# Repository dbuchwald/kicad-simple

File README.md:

# kicad-simple
Simple designs in KiCAD that do not require separate projects

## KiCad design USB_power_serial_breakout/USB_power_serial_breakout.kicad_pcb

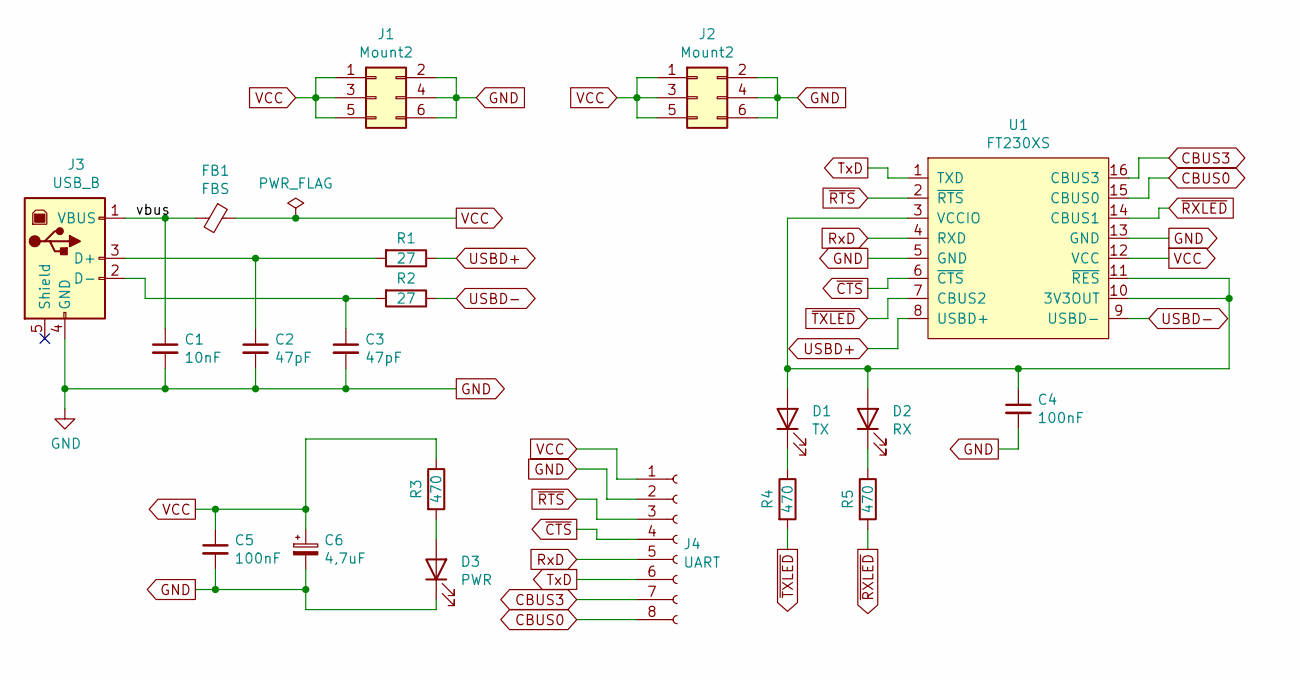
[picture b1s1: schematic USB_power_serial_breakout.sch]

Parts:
C1: 10nF; C_1206_3216Metric_Pad1.33x1.80mm_HandSolder
C2, C3: 47pF; C_1206_3216Metric_Pad1.33x1.80mm_HandSolder
C4, C5: 100nF; C_1206_3216Metric_Pad1.33x1.80mm_HandSolder
C6: 4,7uF; CP_Radial_D4.0mm_P2.00mm
D1: TX; LED_1206_3216Metric_Pad1.42x1.75mm_HandSolder
D2: RX; LED_1206_3216Metric_Pad1.42x1.75mm_HandSolder
D3: PWR; LED_1206_3216Metric_Pad1.42x1.75mm_HandSolder
FB1: FBS; R_1206_3216Metric_Pad1.30x1.75mm_HandSolder
J1, J2: Mount2; PinHeader_2x03_P2.54mm_Vertical
J3: USB_B; USB_B_OST_USB-B1HSxx_Horizontal
J4: UART; PinSocket_1x08_P2.54mm_Vertical
R1, R2: 27; R_1206_3216Metric_Pad1.30x1.75mm_HandSolder
R3, R4, R5: 470; R_1206_3216Metric_Pad1.30x1.75mm_HandSolder
U1: FT230XS; SSOP-16_4.4x5.2mm_P0.65mm

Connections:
/vbus: C1.1, FB1.2, J3.1 (VBUS)
CBUS0: J4.8, U1.15 (CBUS0)
CBUS3: J4.7, U1.16 (CBUS3)
GND: C1.2, C2.2, C3.2, C4.2, C5.2, C6.2, D3.1 (K), J1.2, J1.4, J1.6, J2.2, J2.4, J2.6, J3.4 (GND), J4.2, U1.5 (GND), U1.13 (GND)
unnamed: C2.1, J3.3 (D+), R1.2
unnamed: C3.1, J3.2 (D-), R2.2
unnamed: C4.1, D1.2 (A), D2.2 (A), U1.3 (VCCIO), U1.10 (3V3OUT), U1.11 (~RES)
unnamed: D1.1 (K), R4.1
unnamed: D2.1 (K), R5.1
unnamed: D3.2 (A), R3.2
RxD: J4.5, U1.4 (RXD)
TxD: J4.6, U1.1 (TXD)
USBD+: R1.1, U1.8 (USBD+)
USBD-: R2.1, U1.9 (USBD-)
VCC: C5.1, C6.1, FB1.1, J1.1, J1.3, J1.5, J2.1, J2.3, J2.5, J4.1, R3.1, U1.12 (VCC)
~CTS: J4.4, U1.6 (~CTS)
~RTS: J4.3, U1.2 (~RTS)
~RXLED: R5.2, U1.14 (CBUS1)
~TXLED: R4.2, U1.7 (CBUS2)

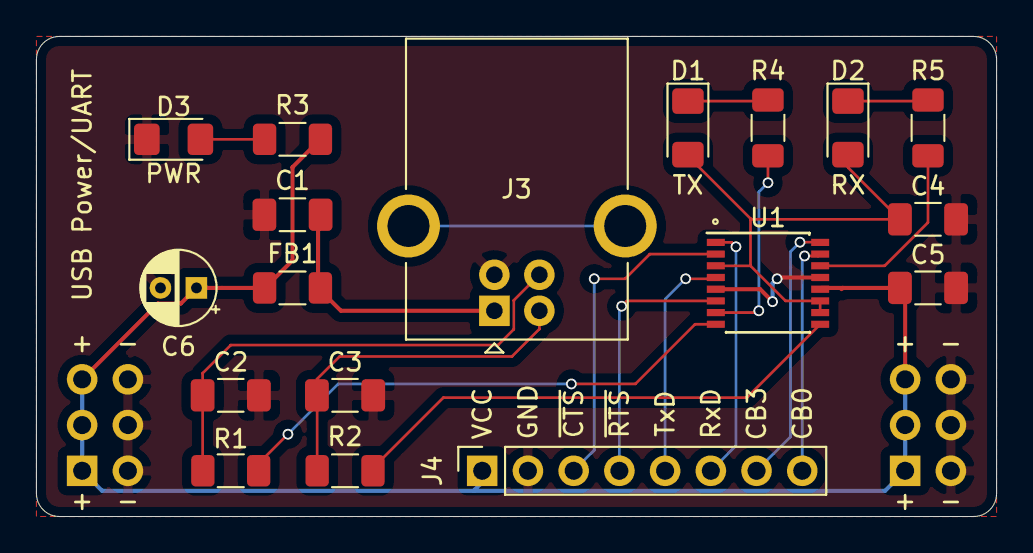
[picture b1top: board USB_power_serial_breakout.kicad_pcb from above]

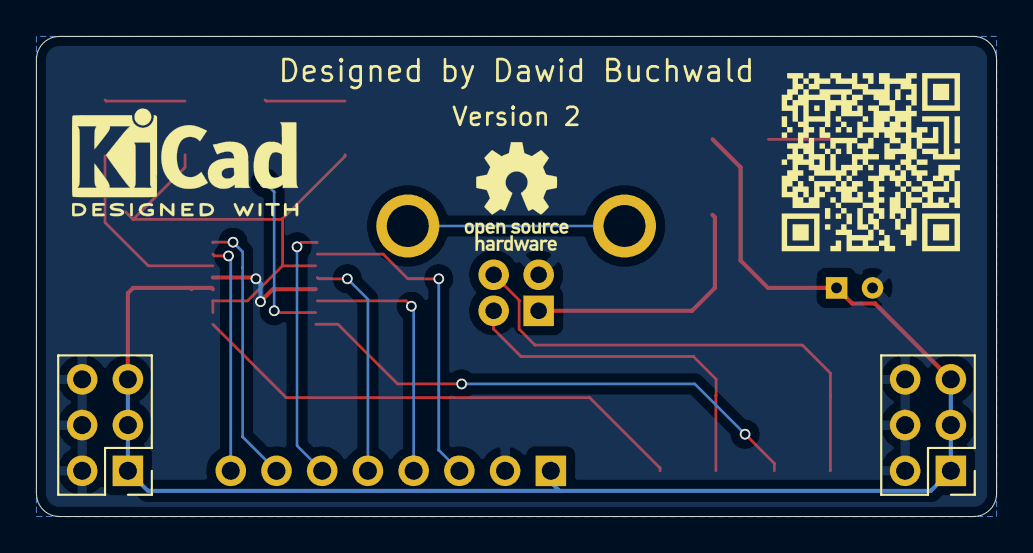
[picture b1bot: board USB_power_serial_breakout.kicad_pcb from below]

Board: 2 copper layers, 53.3 x 26.7 mm, 21 parts (3 on the bottom side), 19 nets.

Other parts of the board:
QR*****: https://tinyurl.com/ghdbks; kicad-simple

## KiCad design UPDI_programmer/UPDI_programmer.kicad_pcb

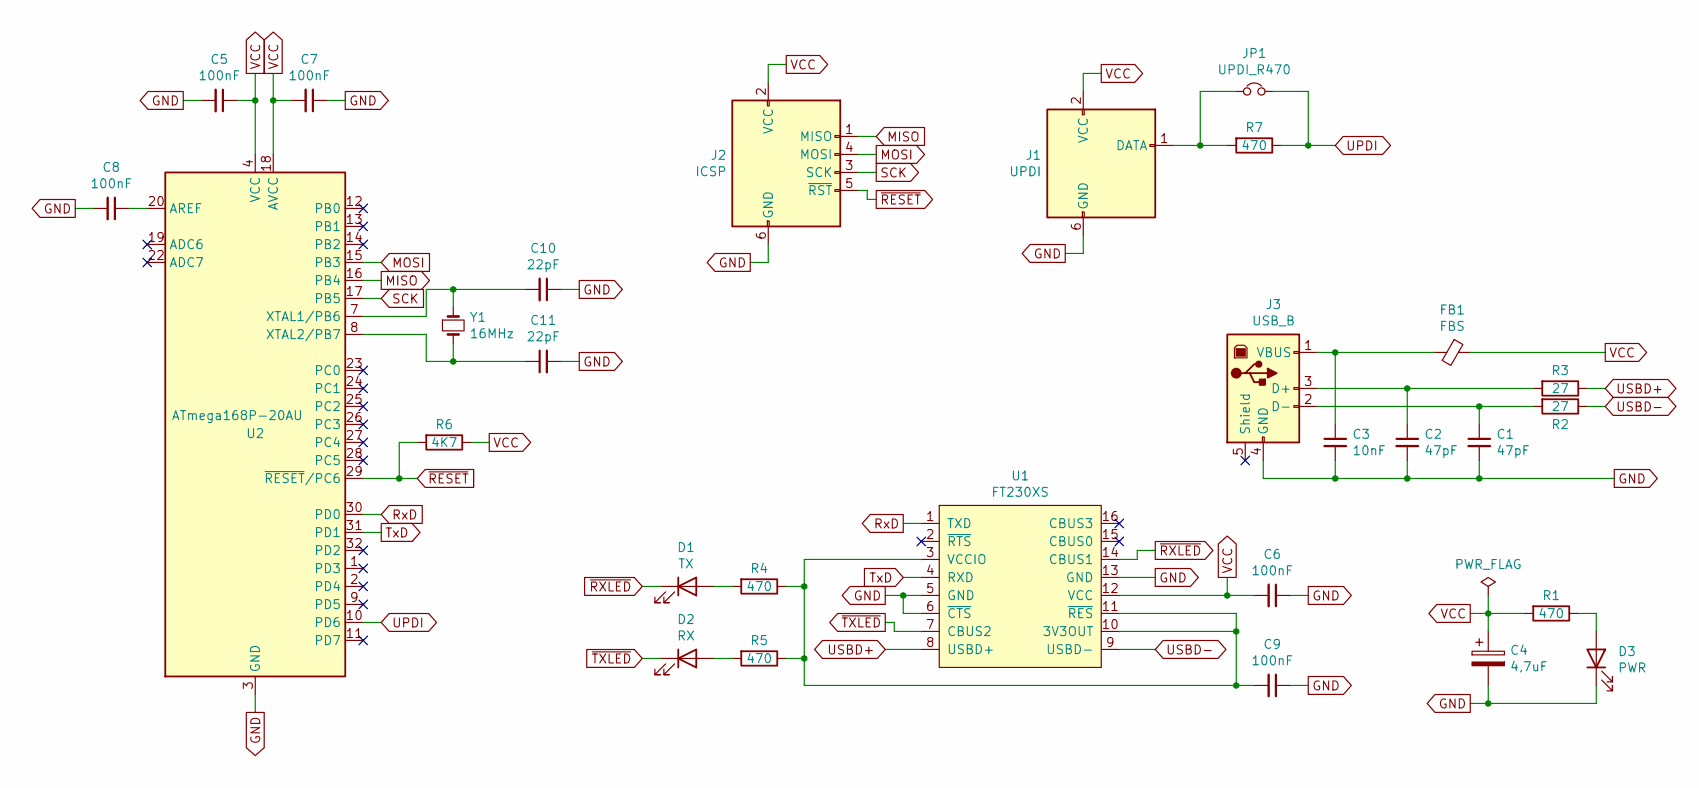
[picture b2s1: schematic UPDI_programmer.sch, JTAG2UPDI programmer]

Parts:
C1, C2: 47pF; C_1206_3216Metric_Pad1.33x1.80mm_HandSolder
C3: 10nF; C_1206_3216Metric_Pad1.33x1.80mm_HandSolder
C4: 4,7uF; CP_Radial_D4.0mm_P2.00mm
C5, C6, C7, C8, C9: 100nF; C_1206_3216Metric_Pad1.33x1.80mm_HandSolder
C10, C11: 22pF; C_1206_3216Metric_Pad1.33x1.80mm_HandSolder
D1: TX; LED_1206_3216Metric_Pad1.42x1.75mm_HandSolder
D2: RX; LED_1206_3216Metric_Pad1.42x1.75mm_HandSolder
D3: PWR; LED_1206_3216Metric_Pad1.42x1.75mm_HandSolder
FB1: FBS; R_1206_3216Metric_Pad1.30x1.75mm_HandSolder
J1: UPDI; IDC-Header_2x03_P2.54mm_Vertical
J2: ICSP; PinHeader_2x03_P2.54mm_Vertical
J3: USB_B; USB_B_OST_USB-B1HSxx_Horizontal
JP1: UPDI_R470; PinHeader_1x02_P2.54mm_Vertical
R1, R4, R5, R7: 470; R_1206_3216Metric_Pad1.30x1.75mm_HandSolder
R2, R3: 27; R_1206_3216Metric_Pad1.30x1.75mm_HandSolder
R6: 4K7; R_1206_3216Metric_Pad1.30x1.75mm_HandSolder
U1: FT230XS; SSOP-16_4.4x5.2mm_P0.65mm
U2: ATmega168P-20AU; TQFP-32_7x7mm_P0.8mm
Y1: 16MHz; Crystal_HC49-U_Vertical

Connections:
GND: C1.2, C2.2, C3.2, C4.2, C5.2, C6.1, C7.1, C8.2, C9.1, C10.1, C11.2, D3.1 (K), J1.6 (GND), J2.6 (GND), J3.4 (GND), U1.5 (GND), U1.6 (~CTS), U1.13 (GND), U2.3 (GND), U2.5 (GND), U2.21 (GND)
MISO: J2.1 (MISO), U2.16 (PB4)
MOSI: J2.4 (MOSI), U2.15 (PB3)
unnamed: C1.1, J3.2 (D-), R2.2
unnamed: C2.1, J3.3 (D+), R3.2
unnamed: C3.1, FB1.2, J3.1 (VBUS)
unnamed: C8.1, U2.20 (AREF)
unnamed: C9.2, R4.1, R5.1, U1.3 (VCCIO), U1.10 (3V3OUT), U1.11 (~RES)
unnamed: C10.2, U2.7 (XTAL1/PB6), Y1.1
unnamed: C11.1, U2.8 (XTAL2/PB7), Y1.2
unnamed: D1.2 (A), R4.2
unnamed: D2.2 (A), R5.2
unnamed: D3.2 (A), R1.1
unnamed: J1.1 (DATA), JP1.1, R7.2
RxD: U1.1 (TXD), U2.30 (PD0)
SCK: J2.3 (SCK), U2.17 (PB5)
TxD: U1.4 (RXD), U2.31 (PD1)
UPDI: JP1.2, R7.1, U2.10 (PD6)
USBD+: R3.1, U1.8 (USBD+)
USBD-: R2.1, U1.9 (USBD-)
VCC: C4.1, C5.1, C6.2, C7.2, FB1.1, J1.2 (VCC), J2.2 (VCC), R1.2, R6.1, U1.12 (VCC), U2.4 (VCC), U2.6 (VCC), U2.18 (AVCC)
~RESET: J2.5 (~RST), R6.2, U2.29 (~RESET~/PC6)
~RXLED: D1.1 (K), U1.14 (CBUS1)
~TXLED: D2.1 (K), U1.7 (CBUS2)

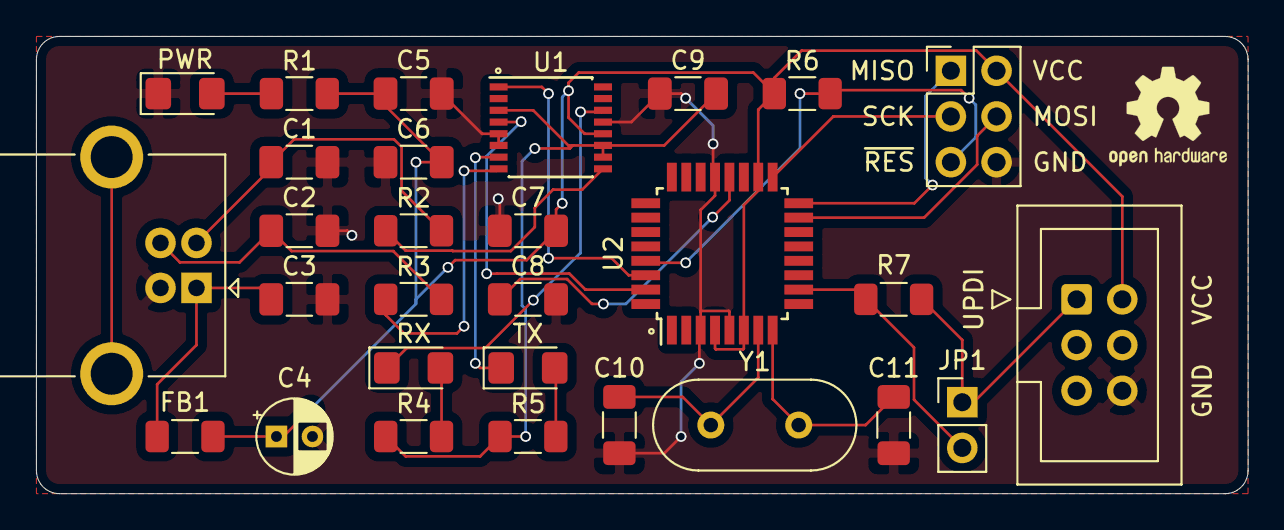
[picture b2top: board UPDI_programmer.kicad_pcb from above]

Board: 2 copper layers, 67.3 x 25.4 mm, 30 parts (1 on the bottom side), 24 nets.

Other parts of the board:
QR*****: https://tinyurl.com/ghdbks; kicad-simple

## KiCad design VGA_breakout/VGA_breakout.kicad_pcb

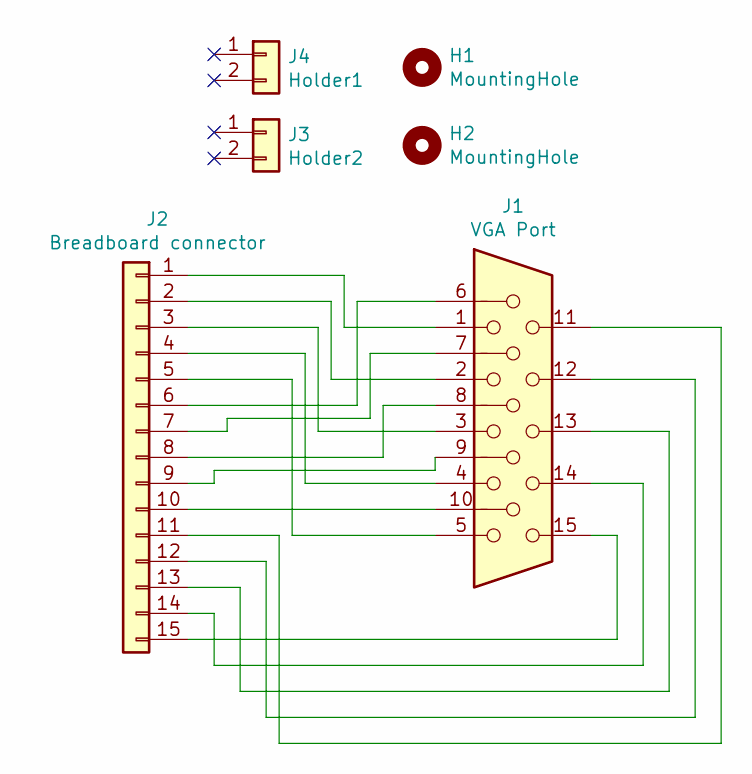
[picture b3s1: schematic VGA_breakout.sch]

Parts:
H1, H2: MountingHole; MountingHole_2mm
J1: VGA Port; ICD15S13E4GV00LF
J2: Breadboard connector; PinHeader_1x15_P2.54mm_Vertical
J3: Holder2; PinHeader_1x02_P2.54mm_Vertical
J4: Holder1; PinHeader_1x02_P2.54mm_Vertical

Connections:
unnamed: J1.1, J2.1
unnamed: J1.2, J2.2
unnamed: J1.3, J2.3
unnamed: J1.4, J2.4
unnamed: J1.5, J2.5
unnamed: J1.6, J2.6
unnamed: J1.7, J2.7
unnamed: J1.8, J2.8
unnamed: J1.9, J2.9
unnamed: J1.10, J2.10
unnamed: J1.11, J2.11
unnamed: J1.12, J2.12
unnamed: J1.13, J2.13
unnamed: J1.14, J2.14
unnamed: J1.15, J2.15

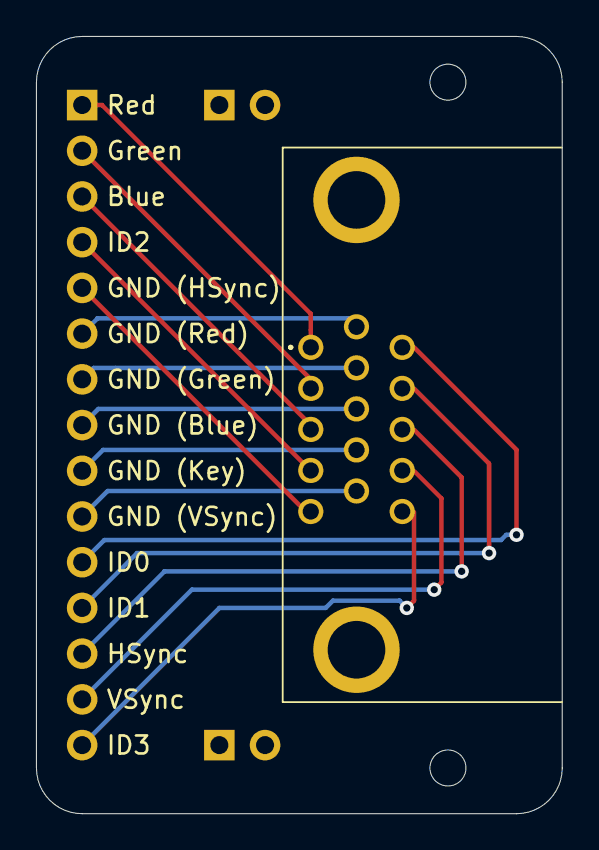
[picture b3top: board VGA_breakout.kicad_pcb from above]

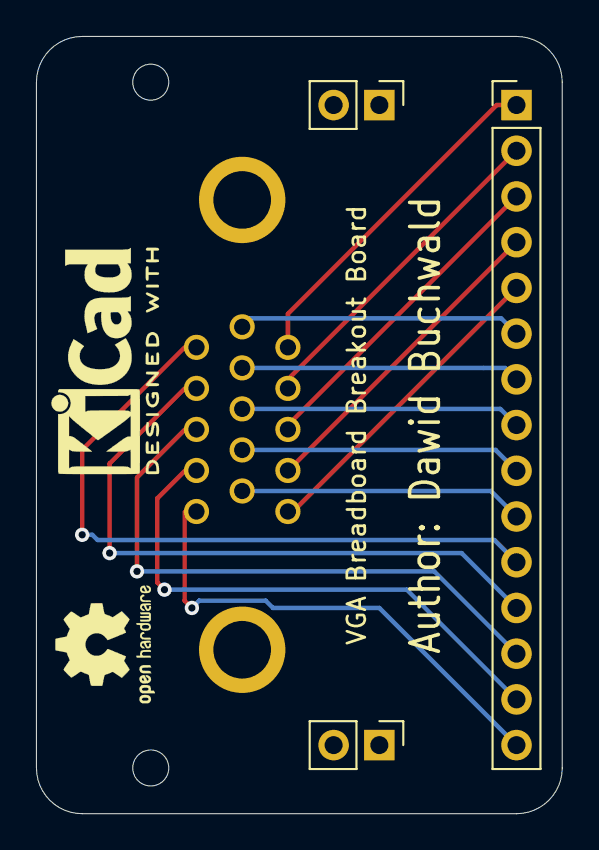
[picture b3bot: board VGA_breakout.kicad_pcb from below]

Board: 2 copper layers, 29.2 x 43.2 mm, 6 parts (3 on the bottom side), 15 nets.

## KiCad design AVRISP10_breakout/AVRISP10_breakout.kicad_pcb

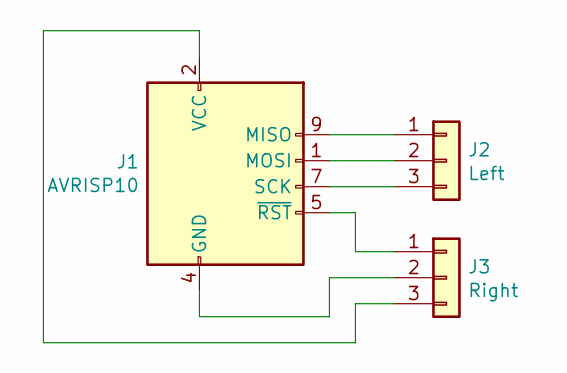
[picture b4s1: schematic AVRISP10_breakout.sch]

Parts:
J1: AVRISP10; PinHeader_2x05_P2.54mm_Vertical
J2: Left; PinHeader_1x03_P2.54mm_Vertical
J3: Right; PinHeader_1x03_P2.54mm_Vertical

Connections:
unnamed: J1.1 (MOSI), J2.2
unnamed: J1.2 (VCC), J3.3
unnamed: J1.5 (~RST), J3.1
unnamed: J1.7 (SCK), J2.3
unnamed: J1.9 (MISO), J2.1
unnamed: J1.4 (GND), J1.6 (GND), J1.8 (GND), J1.10 (GND), J3.2

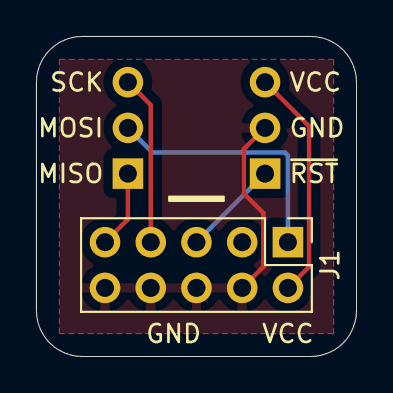
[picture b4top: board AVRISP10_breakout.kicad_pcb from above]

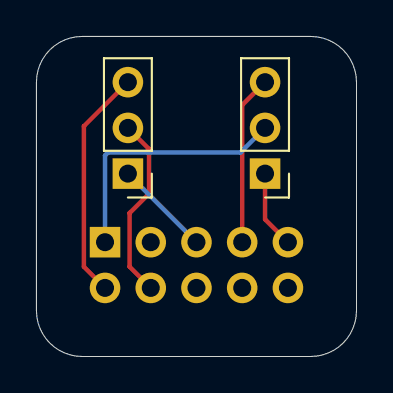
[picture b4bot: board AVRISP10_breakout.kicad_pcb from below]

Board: 2 copper layers, 17.8 x 17.8 mm, 3 parts (2 on the bottom side), 6 nets.

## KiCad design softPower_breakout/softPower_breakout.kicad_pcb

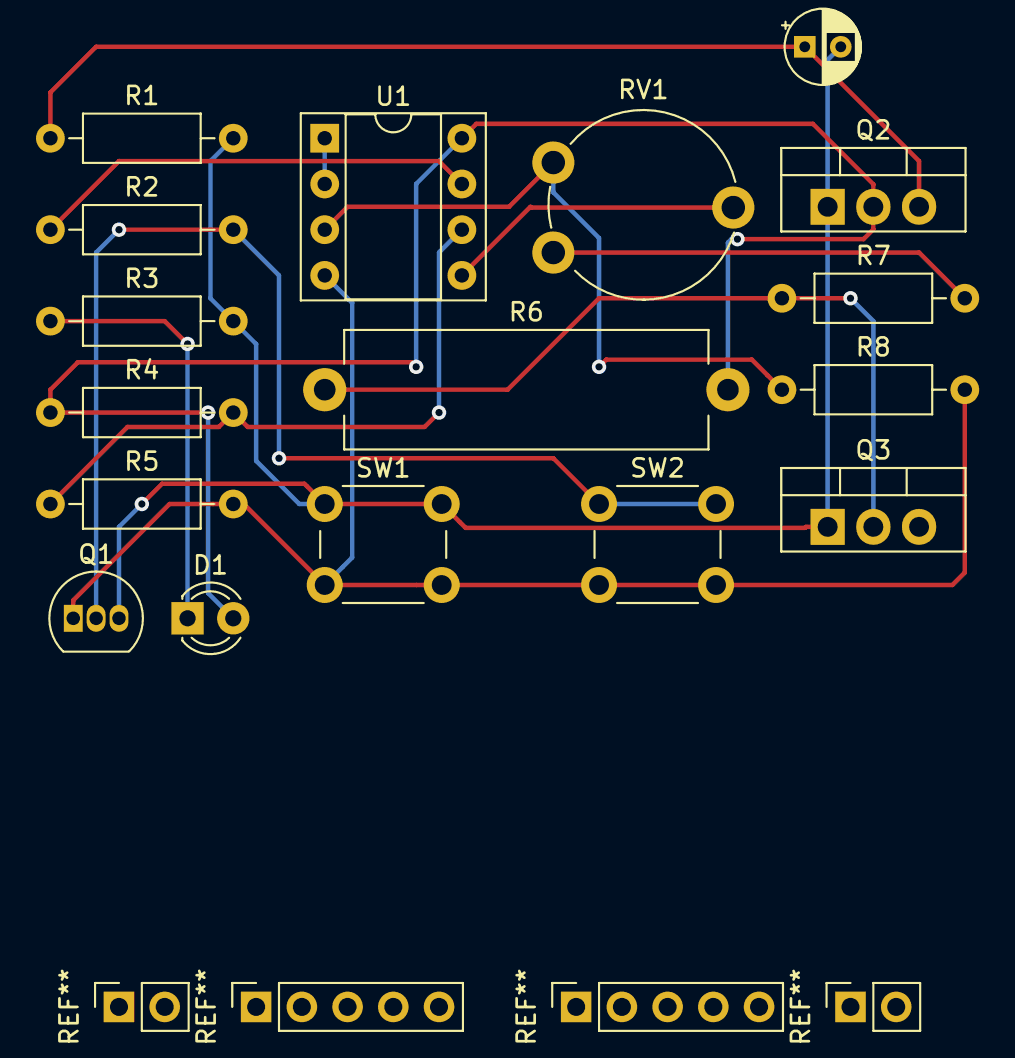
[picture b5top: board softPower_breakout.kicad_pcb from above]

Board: 2 copper layers, 17 parts (0 on the bottom side), 13 nets.

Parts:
C1: 10u; CP_Radial_D4.0mm_P2.00mm
D1: LED; LED_D3.0mm
Q1: 2N3904; TO-92_Inline
Q2, Q3: IRF9540N; TO-220-3_Vertical
R1, R2, R3, R4, R5: 10K; R_Axial_DIN0207_L6.3mm_D2.5mm_P10.16mm_Horizontal
R6: 1; R_Axial_Power_L20.0mm_W6.4mm_P22.40mm
R7, R8: 47K; R_Axial_DIN0207_L6.3mm_D2.5mm_P10.16mm_Horizontal
RV1: 10K; Potentiometer_Piher_PT-10-V10_Vertical
SW1, SW2: SW_Push; SW_PUSH_6mm
U1: TL072; DIP-8_W7.62mm_Socket

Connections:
GND_IN: Q1.1, R5.2, R8.2, SW1.2, SW2.2, U1.4
unnamed: C1.2, Q1.3, Q2.1, Q3.1, R1.2, R3.2, SW1.1
unnamed: D1.1, R3.1
unnamed: D1.2, Q2.2, R4.1, R6.2, U1.8
unnamed: Q1.2, R2.2, SW2.1
unnamed: Q3.2, R6.1, R7.1
unnamed: R2.1, U1.7
unnamed: R4.2, R5.1, U1.6
unnamed: R7.2, RV1.1
unnamed: R8.1, RV1.3, U1.3
unnamed: RV1.2, U1.5
unnamed: U1.1, U1.2
V_IN: C1.1, Q2.3, R1.1

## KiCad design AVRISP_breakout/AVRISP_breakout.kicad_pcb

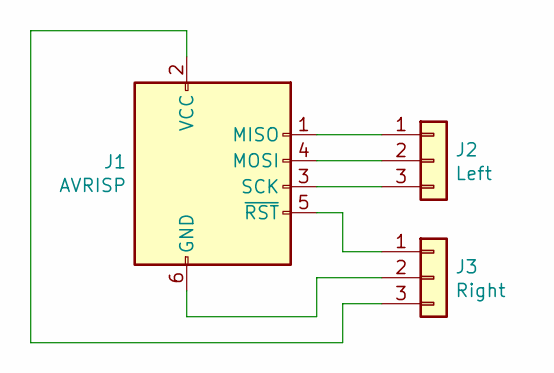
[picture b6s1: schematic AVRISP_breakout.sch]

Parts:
J1: AVRISP; PinHeader_2x03_P2.54mm_Vertical
J2: Left; PinHeader_1x03_P2.54mm_Vertical
J3: Right; PinHeader_1x03_P2.54mm_Vertical

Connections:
unnamed: J1.1 (MISO), J2.1
unnamed: J1.2 (VCC), J3.3
unnamed: J1.3 (SCK), J2.3
unnamed: J1.4 (MOSI), J2.2
unnamed: J1.5 (~RST), J3.1
unnamed: J1.6 (GND), J3.2

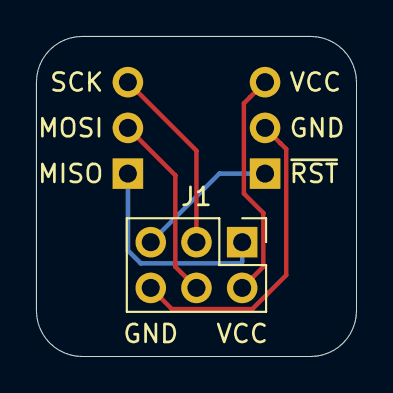
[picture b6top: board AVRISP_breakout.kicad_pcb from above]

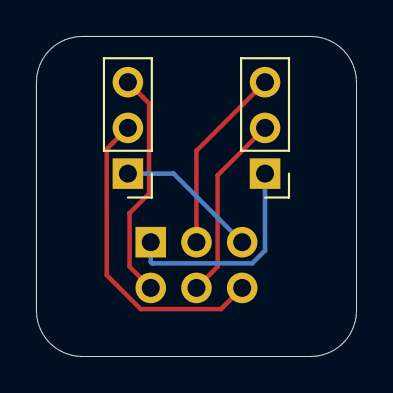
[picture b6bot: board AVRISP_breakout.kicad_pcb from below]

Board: 2 copper layers, 17.8 x 17.8 mm, 3 parts (2 on the bottom side), 6 nets.

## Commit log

2020-11-18 Initial import of the schematics
2020-11-18 Small changes, generated gerber files
2020-11-19 Cosmetic changes to VGA breakout board
2020-11-30 Corrected VGA breakout board DSUB-15 footprint
2021-01-30 Added AVRISP-10 variant
2021-03-19 Initial design for microSD card breakout
2021-03-19 Added initial version of the softPower breakout
2021-05-07 Finalized gerbers for AVRISP10 and VGAv2
2021-05-07 Designed USB PWR/UART breakout
2021-05-08 Updated the USB breakout board
2021-05-10 Replaced UART port labels
2021-05-27 Added sample software for AVRISP testing
2021-05-27 Added sample UART program
2021-10-31 Started working on UPDI programmer
2021-11-01 Finalized schematic
2021-11-01 First PCB draft
2021-11-01 UPDI PCB RC1
2021-11-01 Updated VIA params and changed UPDI resistor
2021-11-02 Added AVR UPDI breakout board
2021-11-02 Updated USB/UART board
2021-11-02 PCB RC2
